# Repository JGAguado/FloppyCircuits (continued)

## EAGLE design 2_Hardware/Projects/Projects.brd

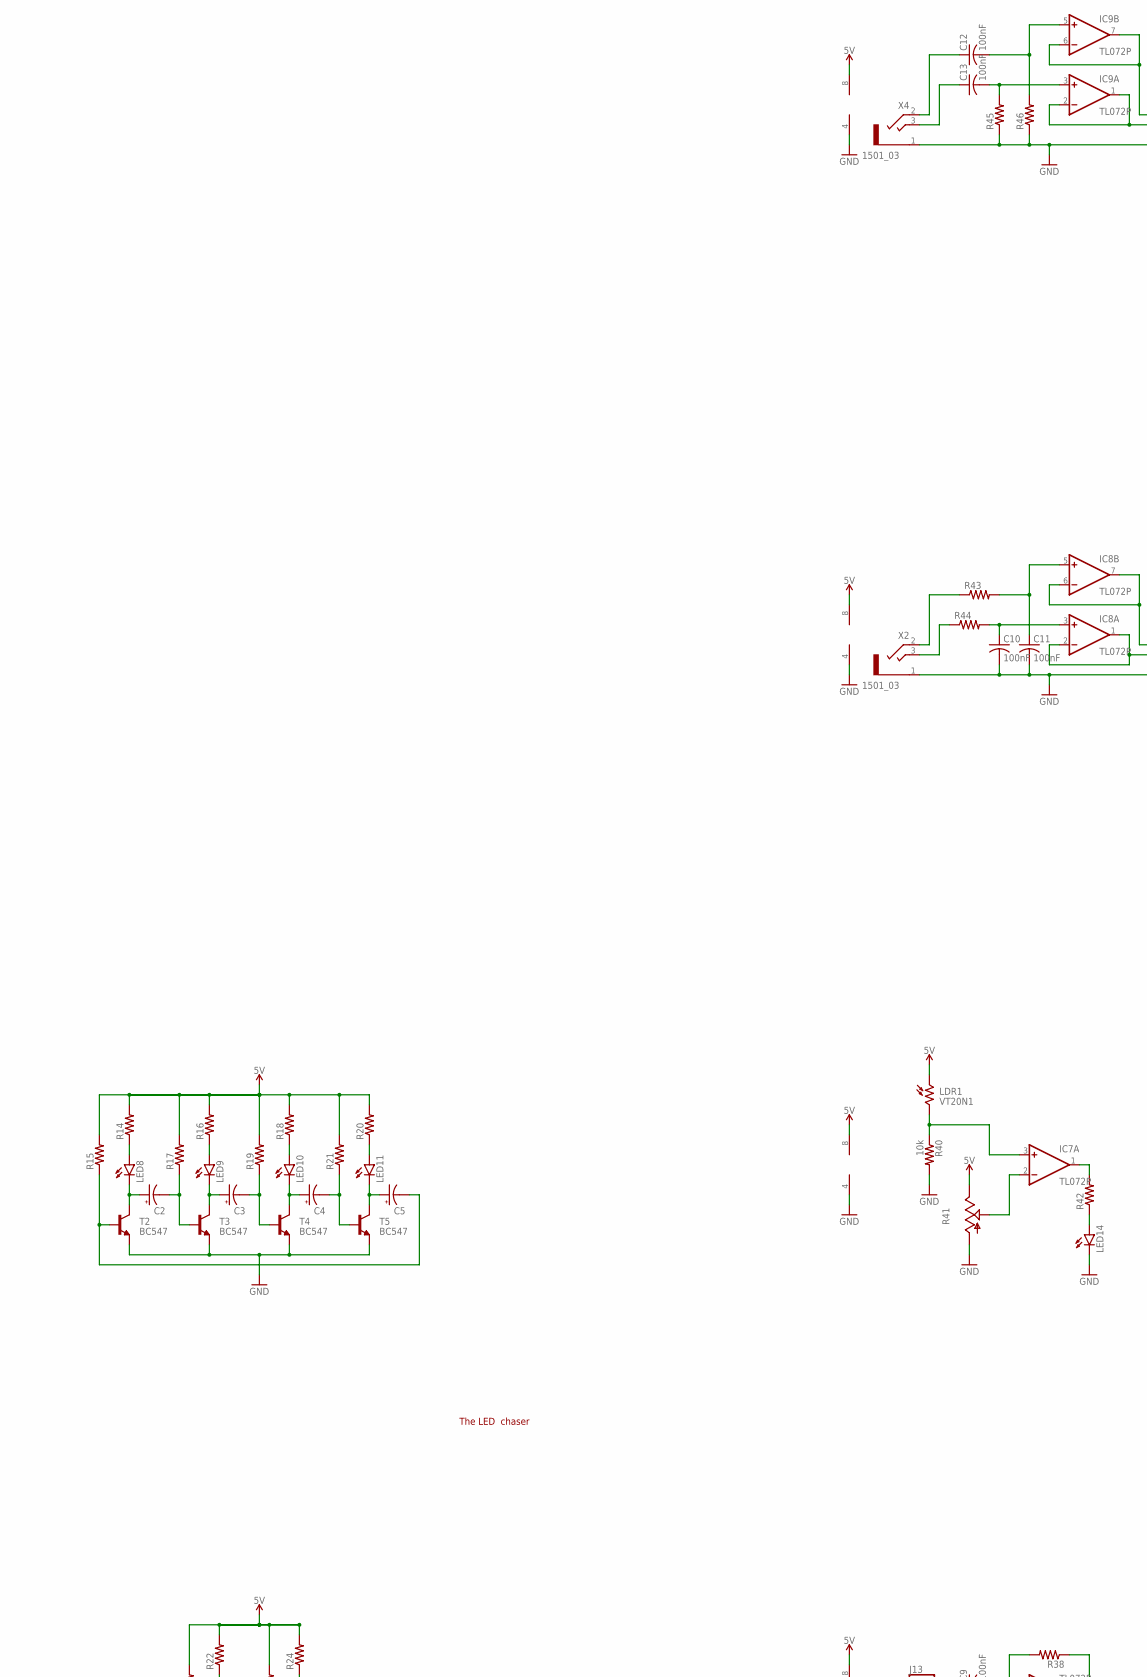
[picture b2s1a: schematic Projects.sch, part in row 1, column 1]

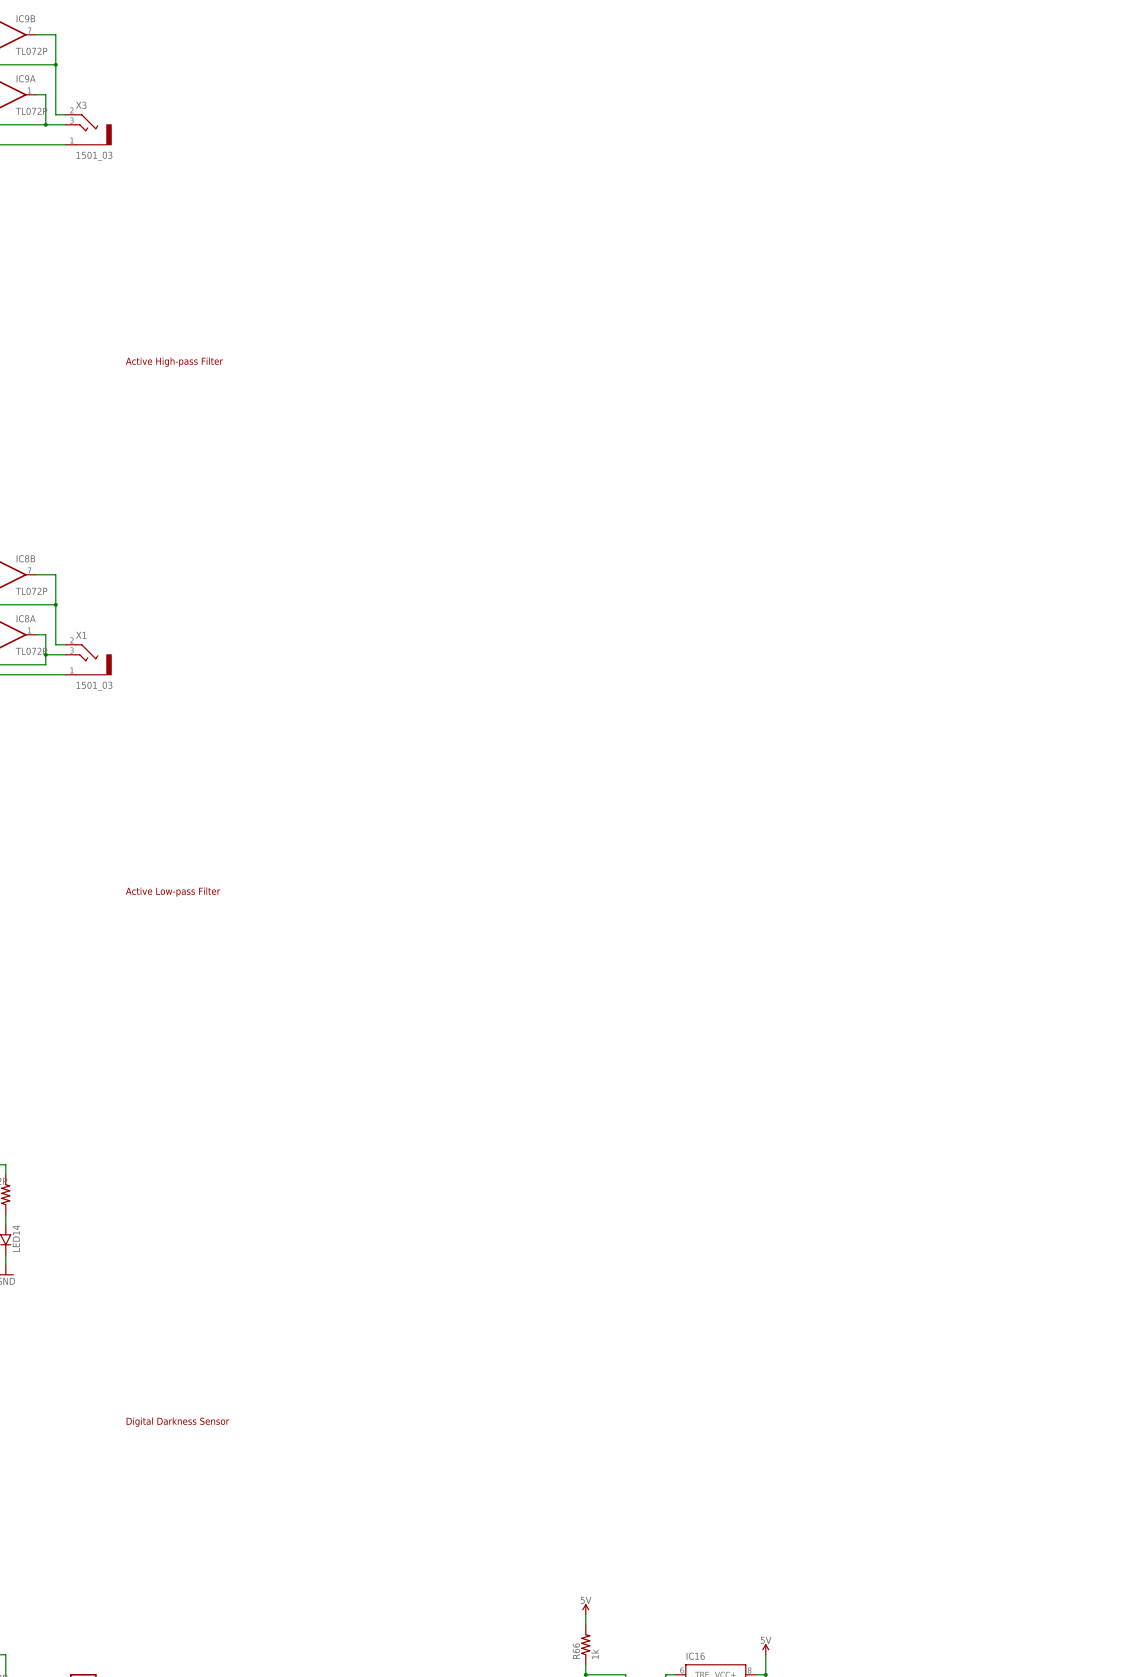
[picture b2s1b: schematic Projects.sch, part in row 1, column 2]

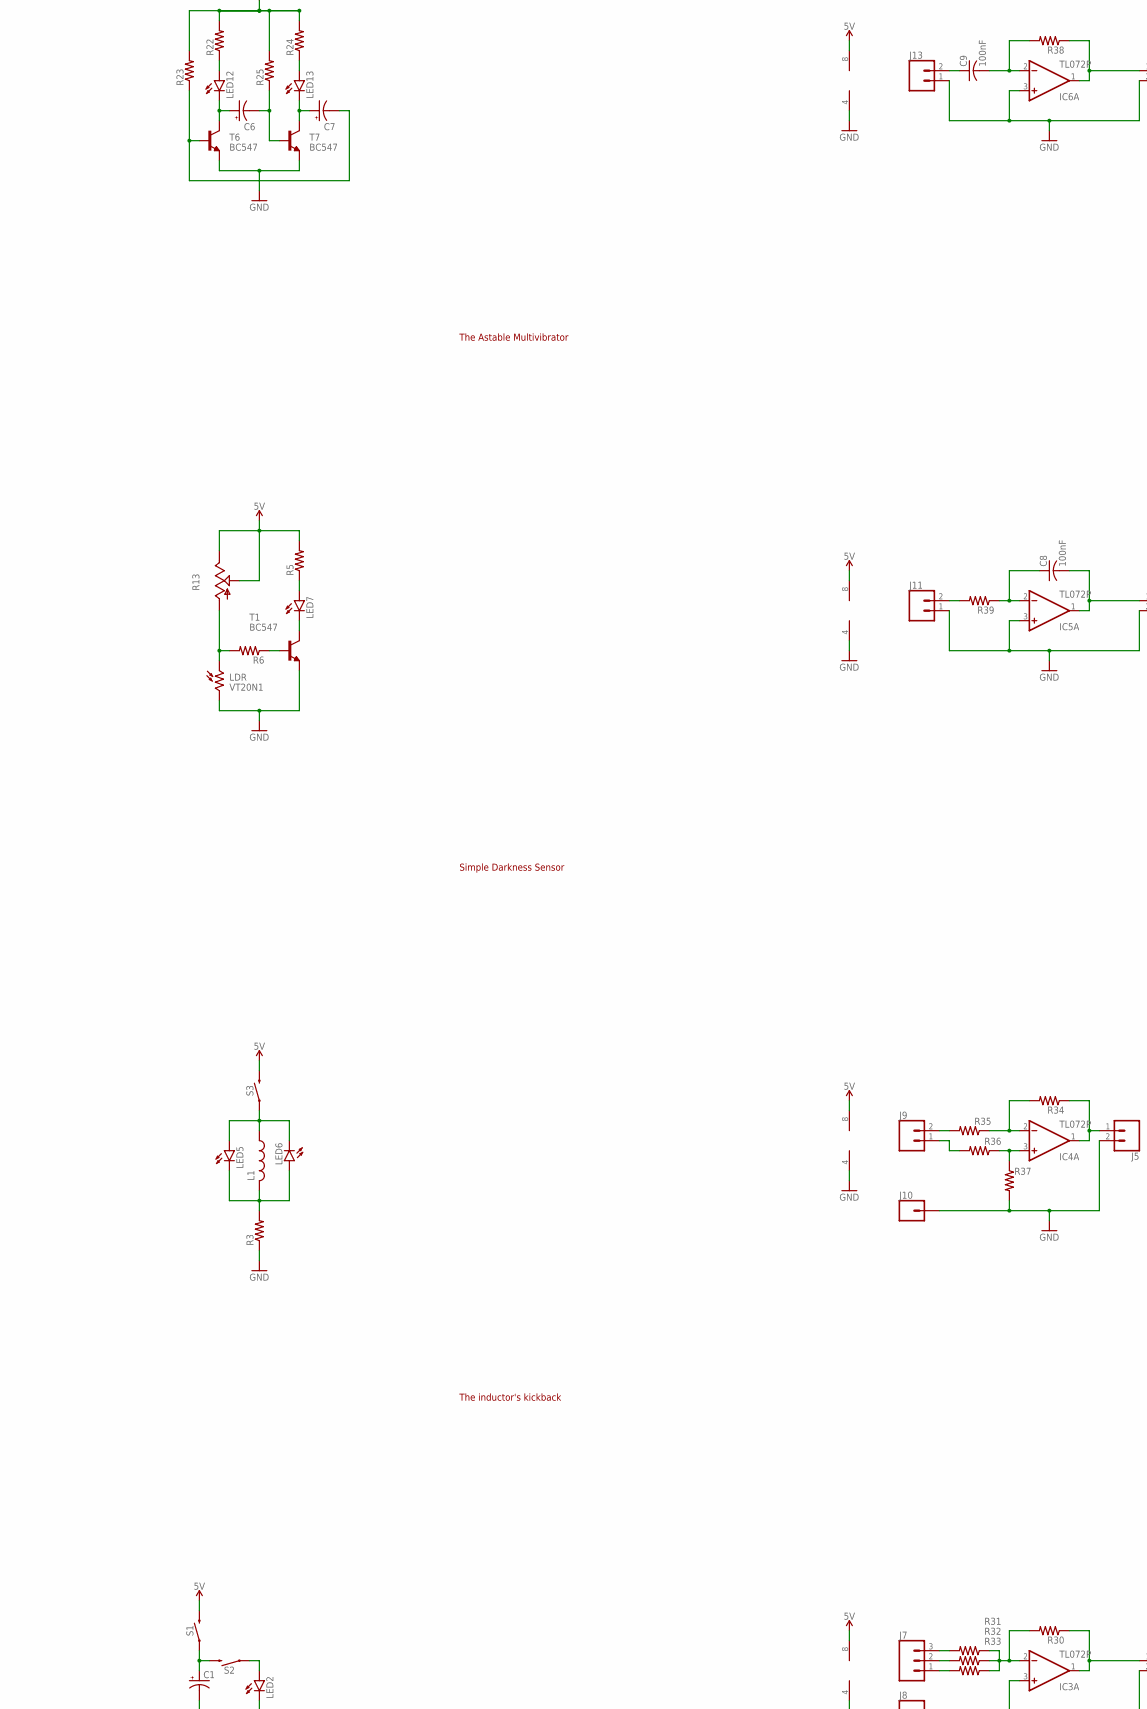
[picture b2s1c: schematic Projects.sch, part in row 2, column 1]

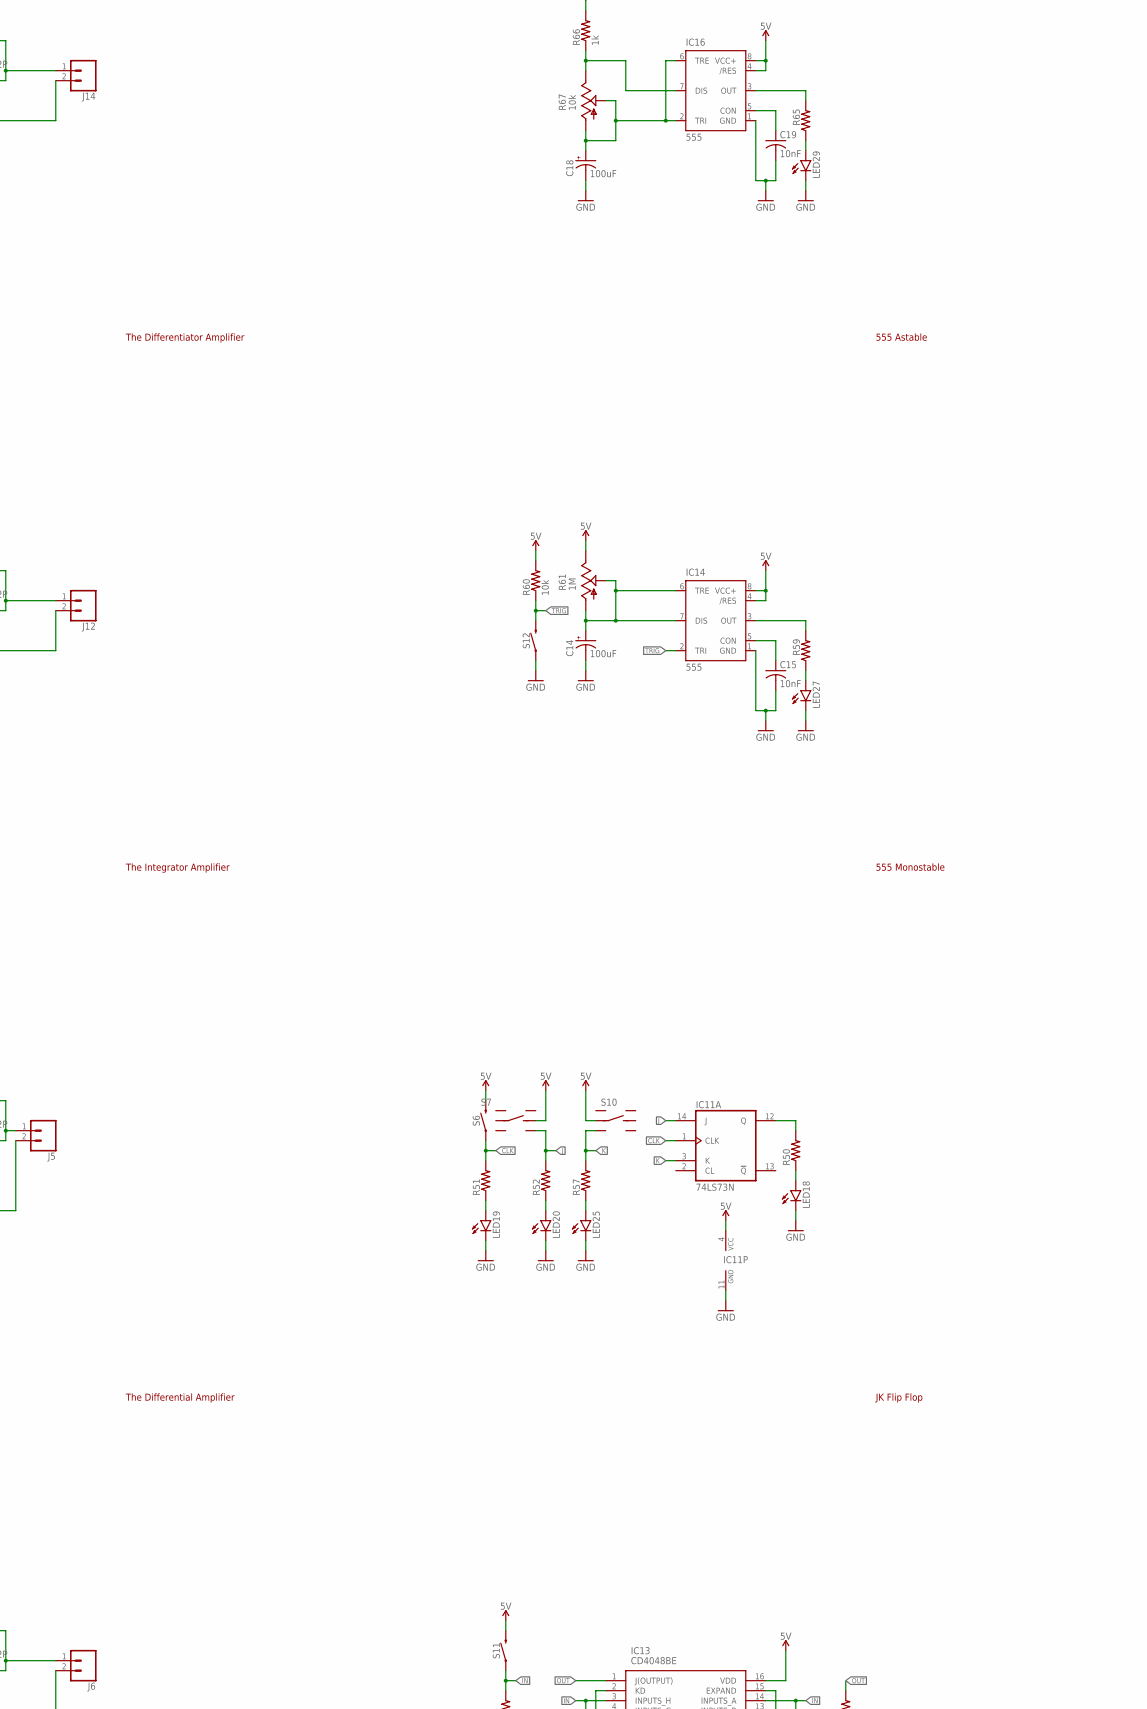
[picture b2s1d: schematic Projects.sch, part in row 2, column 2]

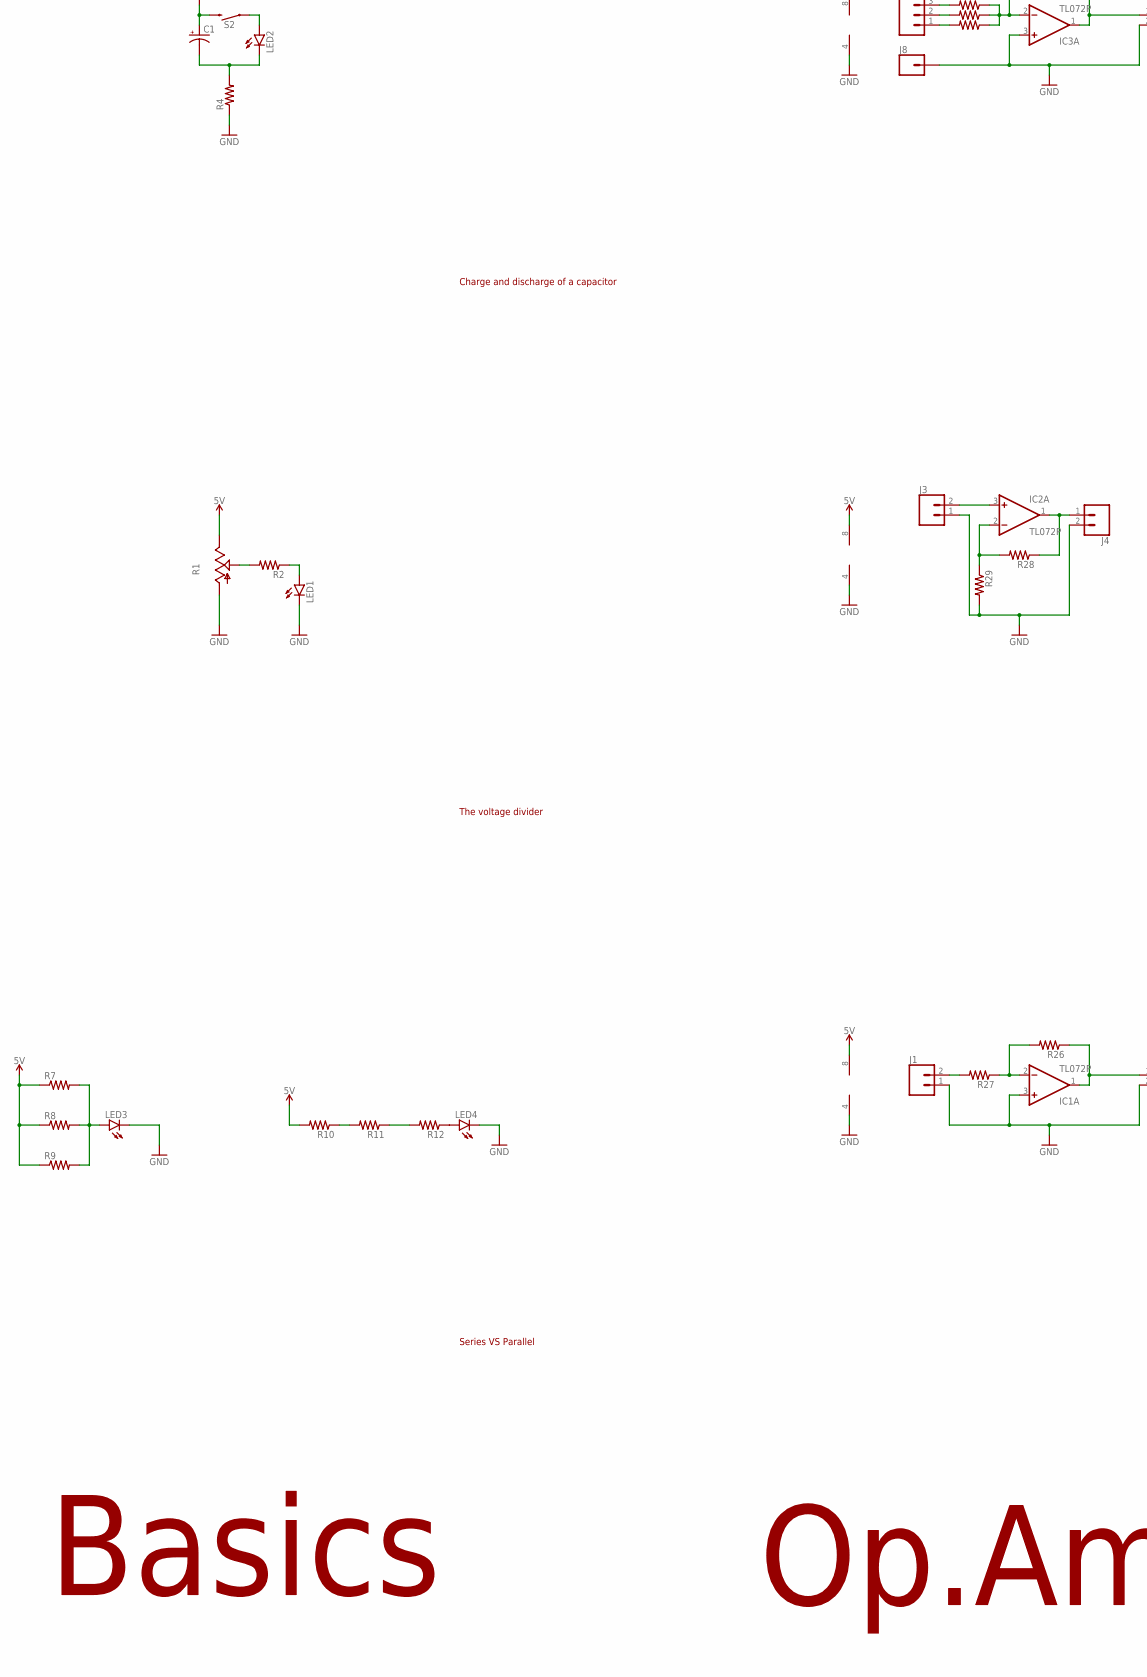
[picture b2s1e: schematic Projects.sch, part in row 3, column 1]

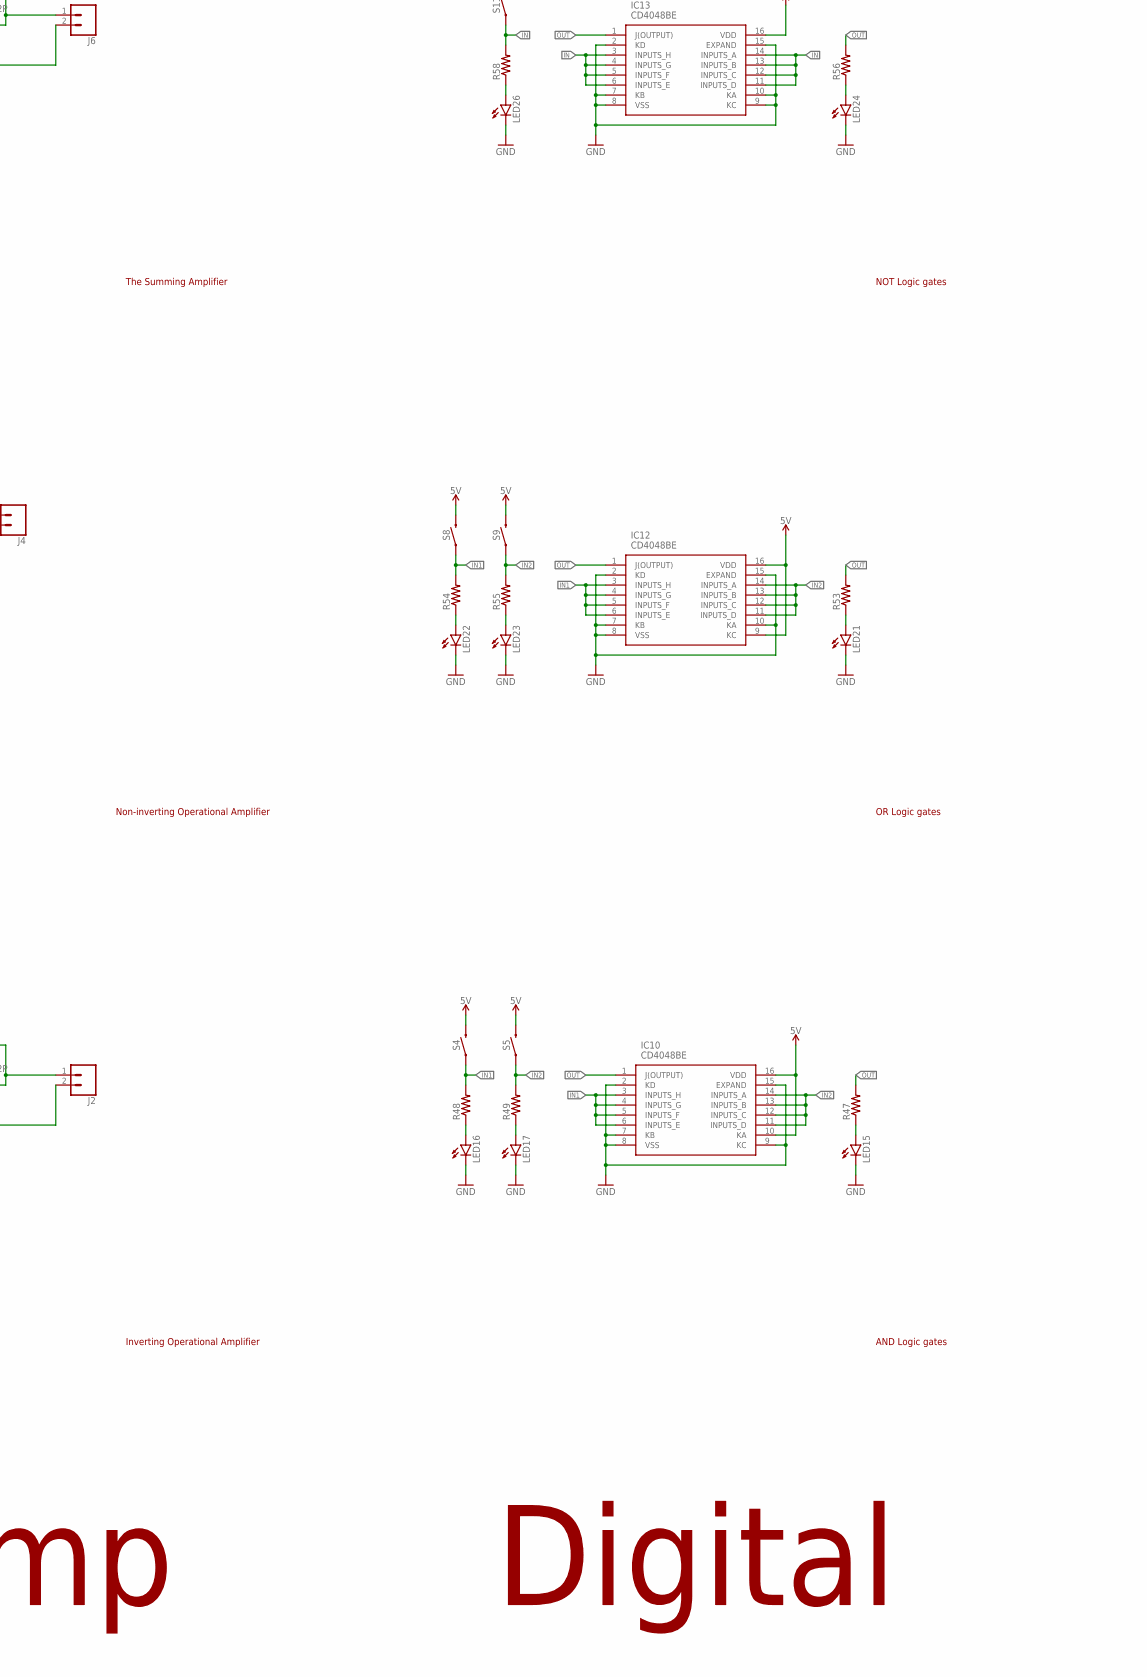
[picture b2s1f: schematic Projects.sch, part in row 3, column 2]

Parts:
C1: CPOL-USE5-10.5; E5-10,5
C2, C3, C4, C5, C6, C7: CPOL-USE2.5-7; E2,5-7
C8, C9, C10, C11, C12, C13: 100nF; C050-025X075
C14, C18: 100uF; E2,5-7
C15, C19: 10nF; C050-025X075
IC1, IC2, IC3, IC4, IC5, IC6, IC7, IC8, IC9: TL072P; DIL08
IC10, IC12, IC13: CD4048BE; DIP794W53P254L1930H508Q16N
IC11: 74LS73N; DIL14
IC14, IC16: 555; DIP08-KIT
J1, J2, J3, J4, J5, J6, J9, J11, J12, J13, J14: CONN_02; 1X02
J7: 455-1750-1-ND; 1X03
J8, J10: CONN_01; 1X01
L1: L-US6000-XXX-RC; 6000-XXXX-RC
LDR, LDR1: VT20N1; TO46-VT200
LED1, LED2, LED3, LED4, LED5, LED6, LED7, LED8, LED9, LED10, LED11, LED12, LED13, LED14, LED15, LED16, LED17, LED18, LED19, LED20, LED21, LED22, LED23, LED24, LED25, LED26, LED27, LED29: LED5MM
R1, R13, R41: TRIM_US-S63P; S63P
R2, R3, R4, R5, R6, R7, R8, R9, R10, R11, R12, R14, R15, R16, R17, R18, R19, R20, R21, R22, R23, R24, R25, R26, R27, R28, R29, R30, R31, R32, R33, R34, R35, R36, R37, R38, R39, R42, R43, R44, R45, R46, R47, R48, R49, R50, R51, R52, R53, R54, R55, R56, R57, R58, R59, R65: R-US_0204/7; 0204/7
R40, R60: 10k; 0204/7
R61: 1M; S63P
R66: 1k; 0204/7
R67: 10k; S63P
S1, S2, S3, S4, S5, S6, S8, S9, S11, S12: MOMENTARY-SWITCH-SPST-PTH-6.0MM; TACTILE_SWITCH_PTH_6.0MM
S7, S10: DPDT_JS202011CQN
T1, T2, T3, T4, T5, T6, T7: BC547; TO92
X1, X2, X3, X4: 1501_03

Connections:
5V: IC1.8 (V+), IC2.8 (V+), IC3.8 (V+), IC4.8 (V+), IC5.8 (V+), IC6.8 (V+), IC7.8 (V+), IC8.8 (V+), IC9.8 (V+), IC10.10 (KA), IC10.16 (VDD), IC11.4 (VCC), IC12.9 (KC), IC12.16 (VDD), IC13.16 (VDD), IC14.4 (/RES), IC14.8 (VCC+), IC16.4 (/RES), IC16.8 (VCC+), LDR1.1, R1.E, R5.2, R7.1, R8.1, R9.1, R10.2, R13.E, R13.S, R14.2, R15.2, R16.2, R17.2, R18.2, R19.2, R20.2, R21.2, R22.2, R23.2, R24.2, R25.2, R41.E, R60.2, R61.E, R66.2, S1.3 (2), S3.3 (2), S4.3 (2), S5.3 (2), S6.3 (2), S7.5 (RC), S8.3 (2), S9.3 (2), S10.2 (LC), S11.3 (2)
CLK: IC11.1 (CLK), R51.2, S6.1
GND: C10.2, C11.2, C14.-, C15.2, C18.-, C19.2, IC1.3 (+IN), IC1.4 (V-), IC2.4 (V-), IC3.3 (+IN), IC3.4 (V-), IC4.4 (V-), IC5.3 (+IN), IC5.4 (V-), IC6.3 (+IN), IC6.4 (V-), IC7.4 (V-), IC8.4 (V-), IC9.4 (V-), IC10.2 (KD), IC10.7 (KB), IC10.8 (VSS), IC10.9 (KC), IC10.15 (EXPAND), IC11.11 (GND), IC12.2 (KD), IC12.7 (KB), IC12.8 (VSS), IC12.10 (KA), IC12.15 (EXPAND), IC13.2 (KD), IC13.7 (KB), IC13.8 (VSS), IC13.9 (KC), IC13.10 (KA), IC13.15 (EXPAND), IC14.1 (GND), IC16.1 (GND), J1.1, J2.2, J3.1, J4.2, J5.2, J6.2, J8.1, J10.1, J11.1, J12.2, J13.1, J14.2, LDR.2, LED1.K (C), LED3.K (C), LED4.K (C), LED14.K (C), LED15.K (C), LED16.K (C), LED17.K (C), LED18.K (C), LED19.K (C), LED20.K (C), LED21.K (C), LED22.K (C), LED23.K (C), LED24.K (C), LED25.K (C), LED26.K (C), LED27.K (C), LED29.K (C), R1.A, R3.1, R4.1, R29.2, R37.2, R40.2, R41.A, R45.1, R46.1, S12.1, T1.1 (E), T2.1 (E), T3.1 (E), T4.1 (E), T5.1 (E), T6.1 (E), T7.1 (E), X1.1, X2.1, X3.1, X4.1
IN: IC13.3 (INPUTS_H), IC13.4 (INPUTS_G), IC13.5 (INPUTS_F), IC13.6 (INPUTS_E), IC13.11 (INPUTS_D), IC13.12 (INPUTS_C), IC13.13 (INPUTS_B), IC13.14 (INPUTS_A), R58.2, S11.1
IN1: IC10.3 (INPUTS_H), IC10.4 (INPUTS_G), IC10.5 (INPUTS_F), IC10.6 (INPUTS_E), IC12.3 (INPUTS_H), IC12.4 (INPUTS_G), IC12.5 (INPUTS_F), IC12.6 (INPUTS_E), R48.2, R54.2, S4.1, S8.1
IN2: IC10.11 (INPUTS_D), IC10.12 (INPUTS_C), IC10.13 (INPUTS_B), IC10.14 (INPUTS_A), IC12.11 (INPUTS_D), IC12.12 (INPUTS_C), IC12.13 (INPUTS_B), IC12.14 (INPUTS_A), R49.2, R55.2, S5.1, S9.1
J: IC11.14 (J), R52.2, S7.6 (R2)
K: IC11.3 (K), R57.2, S10.3 (L2)
unnamed: LED4.A, R12.1
unnamed: R1.S, R2.2
unnamed: LED1.A, R2.1
unnamed: C1.+, S1.1, S2.3 (2)
unnamed: C1.-, LED2.K (C), R4.2
unnamed: R10.1, R11.2
unnamed: R11.1, R12.2
unnamed: LED3.A, R7.2, R8.2, R9.2
unnamed: LED2.A, S2.1
unnamed: L1.1, LED5.A, LED6.K (C), S3.1
unnamed: L1.2, LED5.K (C), LED6.A, R3.2
unnamed: R6.1, T1.2 (B)
unnamed: LDR.1, R6.2, R13.A
unnamed: C6.+, LED12.K (C), T6.3 (C)
unnamed: LED7.K (C), T1.3 (C)
unnamed: LED7.A, R5.1
unnamed: C2.-, R17.1, T3.2 (B)
unnamed: C2.+, LED8.K (C), T2.3 (C)
unnamed: LED8.A, R14.1
unnamed: C3.+, LED9.K (C), T3.3 (C)
unnamed: LED9.A, R16.1
unnamed: IC2.2 (-IN), R28.2, R29.1
unnamed: C3.-, R19.1, T4.2 (B)
unnamed: C4.+, LED10.K (C), T4.3 (C)
unnamed: LED10.A, R18.1
unnamed: IC2.3 (+IN), J3.2
unnamed: C4.-, R21.1, T5.2 (B)
unnamed: C5.+, LED11.K (C), T5.3 (C)
unnamed: LED11.A, R20.1
unnamed: IC1.2 (-IN), R26.2, R27.1
unnamed: C5.-, R15.1, T2.2 (B)
unnamed: LED12.A, R22.1
unnamed: C6.-, R25.1, T7.2 (B)
unnamed: C7.+, LED13.K (C), T7.3 (C)
unnamed: LED13.A, R24.1
unnamed: J1.2, R27.2
unnamed: IC2.1 (OUT), J4.1, R28.1
unnamed: IC3.2 (-IN), R30.2, R31.1, R32.1, R33.1
unnamed: J7.2, R31.2
unnamed: J7.3, R32.2
unnamed: J7.1, R33.2
unnamed: IC1.1 (OUT), J2.1, R26.1
unnamed: IC3.1 (OUT), J6.1, R30.1
unnamed: IC4.2 (-IN), R34.2, R35.1
unnamed: C7.-, R23.1, T6.2 (B)
unnamed: J9.2, R35.2
unnamed: IC4.3 (+IN), R36.1, R37.1
unnamed: J9.1, R36.2
unnamed: IC4.1 (OUT), J5.1, R34.1
unnamed: C8.1, IC5.2 (-IN), R39.1
unnamed: J11.2, R39.2
unnamed: C8.2, IC5.1 (OUT), J12.1
unnamed: C9.2, IC6.2 (-IN), R38.2
unnamed: C9.1, J13.2
unnamed: IC6.1 (OUT), J14.1, R38.1
unnamed: IC7.3 (+IN), LDR1.2, R40.1
unnamed: IC7.2 (-IN), R41.S
unnamed: LED14.A, R42.1
unnamed: IC7.1 (OUT), R42.2
unnamed: R43.1, X2.2
unnamed: R44.1, X2.3
unnamed: C10.1, IC8.3 (+IN), R44.2
unnamed: IC8.1 (OUT), IC8.2 (-IN), X1.3
unnamed: C11.1, IC8.5 (+IN), R43.2
unnamed: IC8.6 (-IN), IC8.7 (OUT), X1.2
unnamed: C12.1, X4.2
unnamed: C13.1, X4.3
unnamed: C13.2, IC9.3 (+IN), R45.2
unnamed: IC9.1 (OUT), IC9.2 (-IN), X3.3
unnamed: C12.2, IC9.5 (+IN), R46.2
unnamed: IC9.6 (-IN), IC9.7 (OUT), X3.2
unnamed: LED16.A, R48.1
unnamed: LED17.A, R49.1
unnamed: LED18.A, R50.1
unnamed: LED15.A, R47.1
unnamed: LED19.A, R51.1
unnamed: LED20.A, R52.1
unnamed: LED21.A, R53.1
unnamed: LED22.A, R54.1
unnamed: LED23.A, R55.1
unnamed: LED24.A, R56.1
unnamed: LED25.A, R57.1
unnamed: LED26.A, R58.1
unnamed: LED27.A, R59.1
unnamed: C15.1, IC14.5 (CON)
unnamed: C14.+, IC14.6 (TRE), IC14.7 (DIS), R61.A, R61.S
unnamed: IC16.7 (DIS), R66.1, R67.E
unnamed: LED29.A, R65.1
unnamed: C19.1, IC16.5 (CON)
OUT: IC10.1 (J(OUTPUT)), IC11.12 (Q), IC12.1 (J(OUTPUT)), IC13.1 (J(OUTPUT)), R47.2, R50.2, R53.2, R56.2
OUT1: IC14.3 (OUT), R59.2
OUT3: IC16.3 (OUT), R65.2
TRIG: C18.+, IC14.2 (TRI), IC16.2 (TRI), IC16.6 (TRE), R60.1, R67.A, R67.S, S12.3 (2)

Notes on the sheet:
Inverting Operational Amplifier
Non-inverting Operational Amplifier
The Summing Amplifier
The Differential Amplifier
The Integrator Amplifier
The Differentiator Amplifier
Series VS Parallel
The voltage divider
Charge and discharge of a capacitor
The inductor's kickback
Simple Darkness Sensor
The Astable Multivibrator
The LED chaser
Digital Darkness Sensor
Basics
Op.Amp
Active Low-pass Filter
Active High-pass Filter
AND Logic gates
Digital
OR Logic gates
NOT Logic gates
JK Flip Flop
555 Monostable
555 Astable

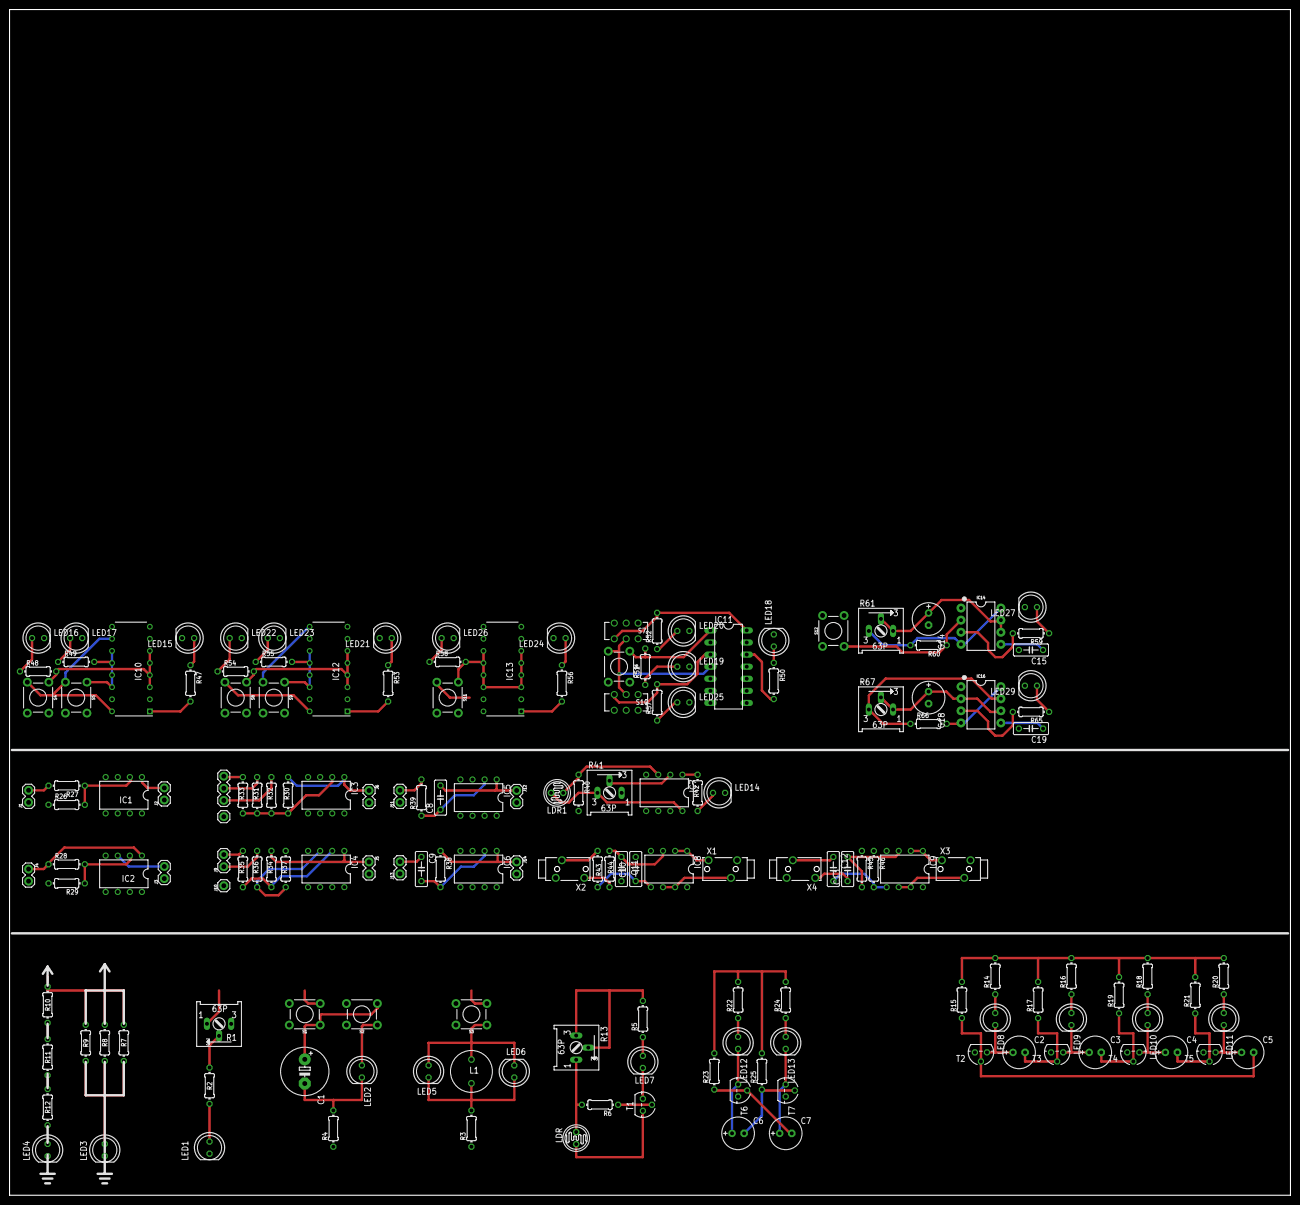
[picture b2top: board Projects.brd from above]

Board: 2 copper layers, 269.0 x 249.0 mm, 164 parts (0 on the bottom side), 101 nets.

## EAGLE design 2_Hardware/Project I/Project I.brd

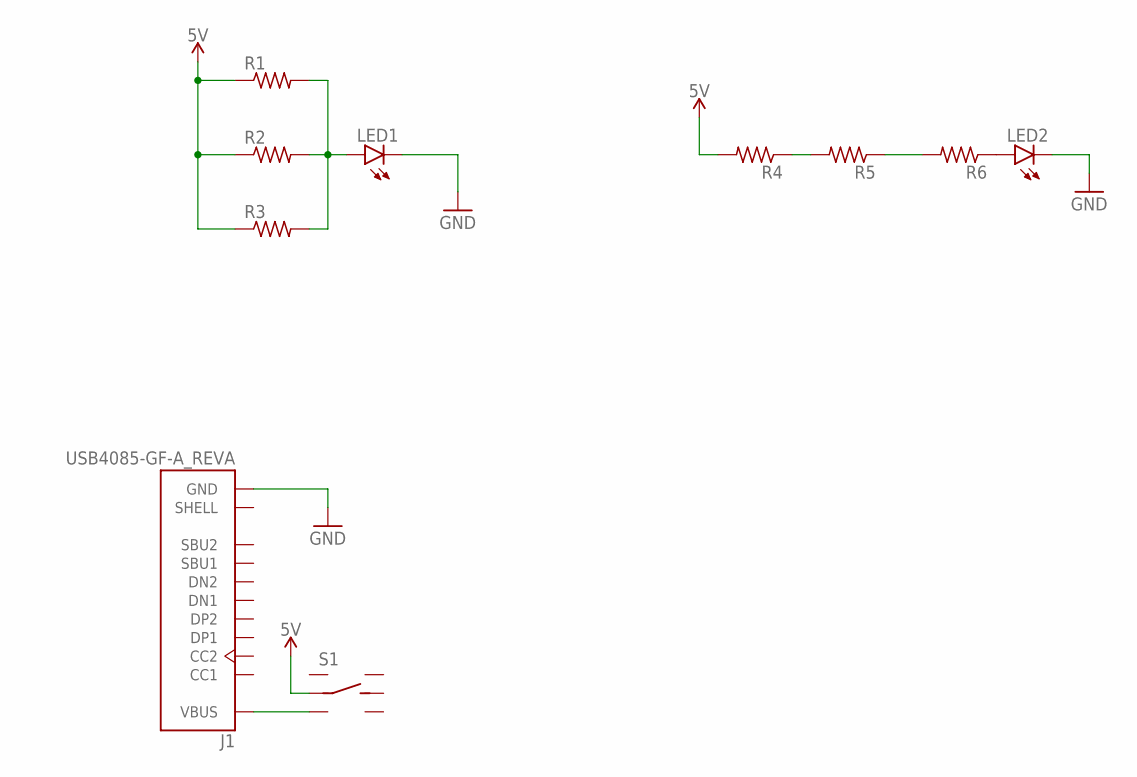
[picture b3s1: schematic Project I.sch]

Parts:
J1: USB4085-GF-A_REVA; GCT_USB4085-GF-A_REVA
LED1, LED2: LED5MM
R1, R2, R3, R4, R5, R6: R-US_0204/7; 0204/7
S1: DPDT_JS202011CQN

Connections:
5V: R1.1, R2.1, R3.1, R4.2, S1.2 (LC)
GND: J1.A1 (GND), J1.A12 (GND), J1.B1 (GND), J1.B12 (GND), LED1.K (C), LED2.K (C)
unnamed: R4.1, R5.2
unnamed: R5.1, R6.2
unnamed: LED1.A, R1.2, R2.2, R3.2
unnamed: LED2.A, R6.1
unnamed: J1.A4 (VBUS), J1.A9 (VBUS), J1.B4 (VBUS), J1.B9 (VBUS), S1.3 (L2)

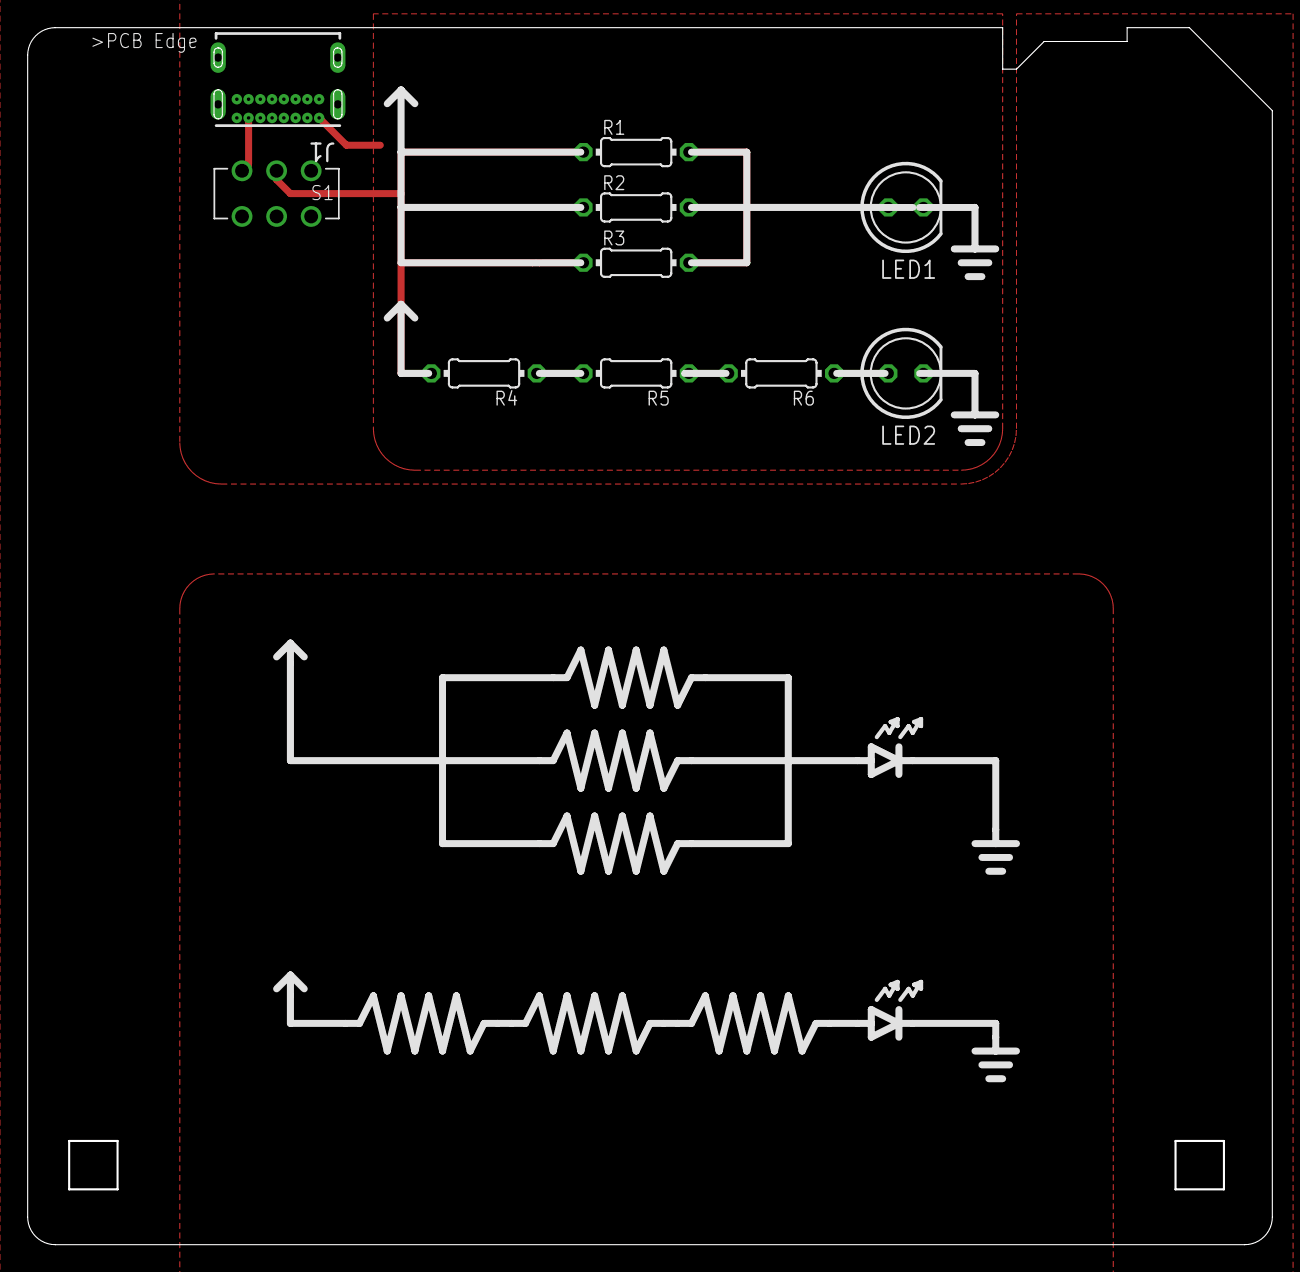
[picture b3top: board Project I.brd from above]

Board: 2 copper layers, 90.0 x 88.0 mm, 22 parts (0 on the bottom side), 7 nets.

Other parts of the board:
U$1, U$5: GND
U$2, U$6: VCC
U$3, U$12: LED
U$4, U$7, U$8, U$9, U$10, U$11: RESISTOR

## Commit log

2021-11-21 First commit to Floppy Circuits
2022-10-09 Updated hardware with Projects, Template and X01-ESP32_Oscilloscope
2022-10-09 * Updated hardware with Projects, Template and X01-ESP32_Oscilloscope
